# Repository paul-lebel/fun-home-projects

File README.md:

# fun-home-projects
A small platform for parent-configurable child entertainment and education.

## Features
1. A small box with a simple screen, UI buttons, an audio system, and a lighting system.
2. A software platform that allows parents to create custom quiz questions (eg. "What does 5+5 equal?") or games.
3. A text to speech module reads the input prompts aloud through the audio speaker for children too young to read.
4. A bluetooth module allows for music streaming to the device from a parent's cellphone.
5. Computer control of the lighting system enhances the user experience for the child.
6. Customization of the underlying PCB's silkscreen artwork is displayed through a transparent front panel.

## Top level requirements
RPi.GPIO, inky, gTTS, circuitpython, adafruit-circuitpython-neopixel

## Installation
This module was developed on Raspberry Pi Zero W V1.1, but should be compatible with all newer RPi models running the latest version of Raspbian OS.
1. Ensure the OS is updated, and also ensure that Python 3 is used by default. Following the instructions here takes care of this as well as circuitpython installation: https://learn.adafruit.com/circuitpython-on-raspberrypi-linux/installing-circuitpython-on-raspberry-pi
2. Follow these instructions to install inky: https://learn.pimoroni.com/tutorial/sandyj/getting-started-with-inky-phat
3. Install this module:

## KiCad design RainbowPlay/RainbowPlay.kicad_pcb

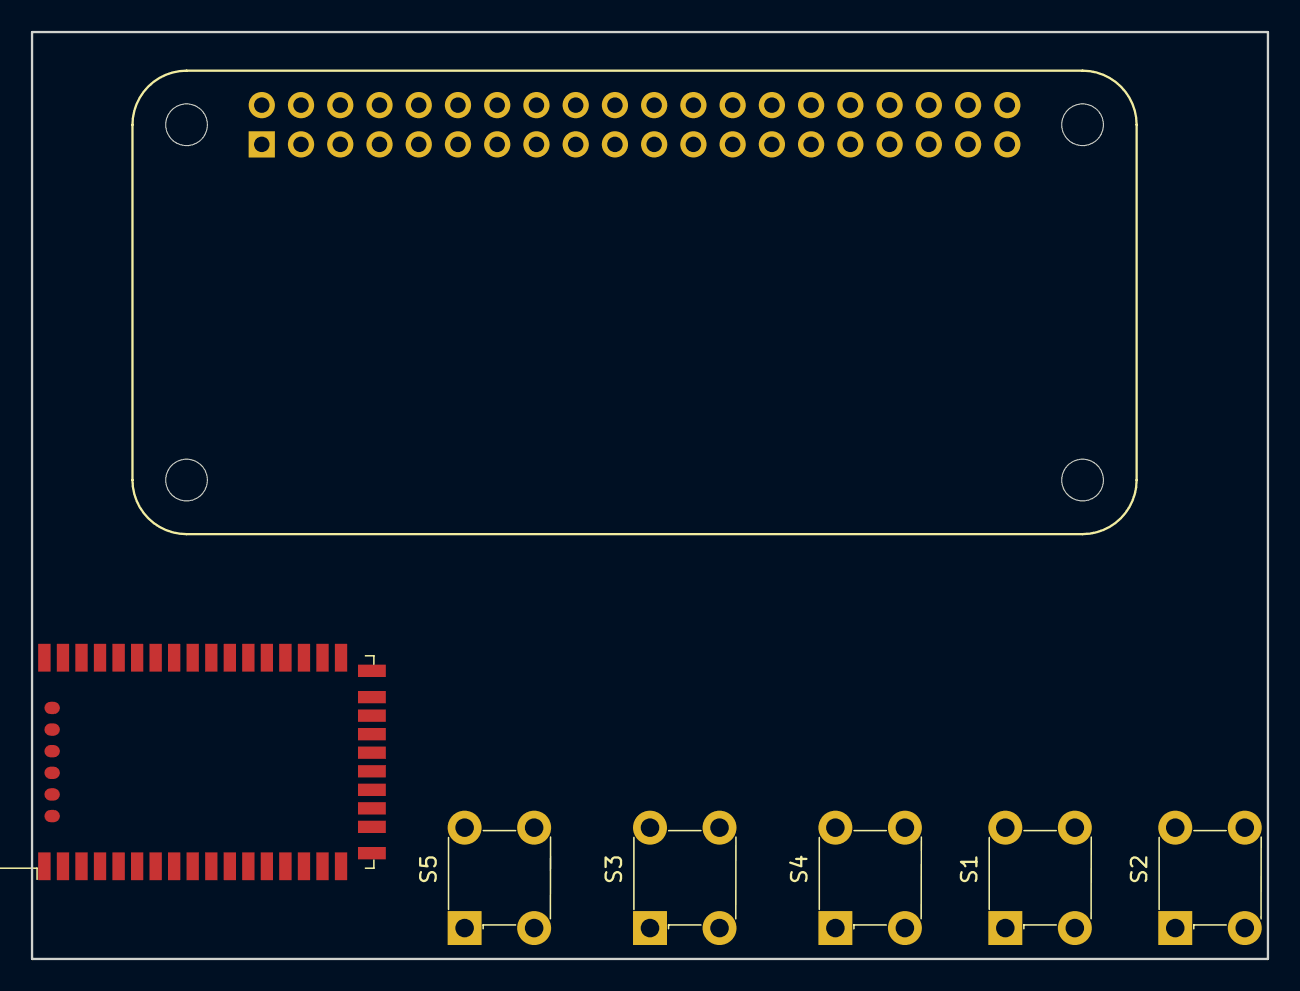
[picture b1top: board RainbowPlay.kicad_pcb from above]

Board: 2 copper layers, 80.0 x 60.0 mm, 11 parts (1 on the bottom side), 10 nets, no tracks yet.

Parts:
H1, H2, H3, H4: MountingHole; MountingHole_2.7mm_M2.5_uHAT_RPi
J1: GPIO_CONNECTOR; PinSocket_2x20_P2.54mm_Vertical_Centered_Anchor
MOD1: RN52-I_RM; Bluetooth_Module_RN52-IRM
S1, S2, S3, S4, S5: 1825910-6; Switch_Tactile_THT_6x6mm

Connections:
+3V3: J1.1, J1.17, MOD1.22
+5V: J1.2, J1.4
/GPIO14_TXD0: J1.8, MOD1.17
/GPIO15_RXD0: J1.10, MOD1.15
/NXT_TRK: MOD1.7, S4.2
/PLY_PS: MOD1.8, S5.2
/PREV_TRK: MOD1.9, S3.2
/VOL_DWN: MOD1.10, S2.2
/VOL_UP: MOD1.6, S1.2
GND: J1.6, J1.9, J1.14, J1.20, J1.25, J1.30, J1.34, J1.39, S1.4, S2.4, S3.4, S4.4, S5.4

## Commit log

2021-01-02 General dev on PCB
    Ensure GPIO pinouts are correct

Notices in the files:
RainbowPlay/RainbowPlay.kicad_pcb:
This PCB design is licensed under MIT Open Source License.
